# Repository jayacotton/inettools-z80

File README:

Here are the first hacks at getting some inet like tools running on
CP/M.

I am using (borrowing/stealing) code from several places.  See source for details.

A lot of hacking went into getting the code to run.  Probably some self inflicted
injuries along the way.

The programs of interest are linked by the Make file.

I am using z88dk and the tool chain.

You will need to hunt down and change the mac address in every file
you can find and in some cases a hard coded ip address.
I will get around to fixing this at a latter date.  

make clean; make ; make install  Gets the programs to build
and copies them to /var/www/html/

With this and apache2 you can get wget running from your 
CP/M machine.  

Programs in this build,  Note:  these don't work like there unix 
big brothers.  

	DIG.COM
		C>dig www.google.com                                                            
		WWW.GOOGLE.COM :172.217.6.36     
	IFCONFIG.COM
		C>ifconfig                                                                      
		inet 192.168.1.129 netmask 255.255.255.0                                        
		ether 98.76.b6.11.00.c4      
	MYGET.COM
		c>myget <filename>
		this will copy a file from your local http server at a
		hard coded address.  (you will need to change the address
		for your network).
	PING.COM
		C>ping www.nasa.gov                                                             
		------------PING_TEST_START-----------------------                              
		Send Ping Request to Destination (13.35.125.62 ) ID:1234  SeqNum:4321 CheckSum:a
		Reply from 13.35.125.62  ID:1234 SeqNum:4321  :data size 52 bytes               
                                                                                
		Send Ping Request to Destination (13.35.125.62 ) ID:1235  SeqNum:4322 CheckSum:8
		Reply from 13.35.125.62  ID:1235 SeqNum:4322  :data size 52 bytes               
                                                                                
		Send Ping Request to Destination (13.35.125.62 ) ID:1236  SeqNum:4323 CheckSum:6
		Reply from 13.35.125.62  ID:1236 SeqNum:4323  :data size 52 bytes               
                                                                                
		-----------PING TEST OK----------                                               
	TELNET.COM
		c>telnet <server name/inet address>
			bla bla bla
		exit (assumes your server does shell exit)
	WGET.COM
		c> wget http://<url or inet address> filename
		copies a file from the server to your CP/M box.

All of these programs are a bit shaky or just plain buggy.  

The socket libraries are kinda broken.  If you are used to BSD sockets you will get into 
trouble real fast.  I am thinking about fixing some of the more obvious bugs and mistakes
...maybe next month...  The main reason to fix these libs, is it then gets easier to port
code to CP/M.

WRT the h/w.

I coded all this to run with my bit banger SPI bus card and an Adafruit wiznet w5500 
ethernet board.  I am planning to build up a h/w SPI board soon, and will make a unified
driver for both cards.  If I can figure out how to do it (correctly) I will be able to
run the programs on ether SPI card with no modification (recompile) needed.  That would
be very nice to do.

Work to be done:

Fix the socket library.
Get some kind of timer code running with the ctc board.
Figure out a good select method.
Unified SPI driver.
Try to get the w5500 driver to work with the w5100 chip.  (it should but wont).

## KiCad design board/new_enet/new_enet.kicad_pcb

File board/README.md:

In this section we have the BOM for the MT011 board as built
for my needs.

For the best and current information about the MT011 board see
https://github.com/markt4311/MT011.git

Find here the mt011-bom.ods a spread sheet for the BOM of the board.
And the schematic (copied from above) MT011_SPI_WIZNET.pdf

I will include a picture of the board as built.

This board is now working on 18mhz cpu rc2014 systems.

```
--------------NOTICE---------------------
--------------NOTICE---------------------
--------------NOTICE---------------------
--------------NOTICE---------------------
--------------NOTICE---------------------
There is a small rework to get an access status led for the enet board.
Look at the schmatic, The resistor R2 leg that connects to pin 7
of U3 should be moved to pin 10 of U3.
--------------NOTICE---------------------
--------------NOTICE---------------------
--------------NOTICE---------------------
--------------NOTICE---------------------
--------------NOTICE---------------------
```

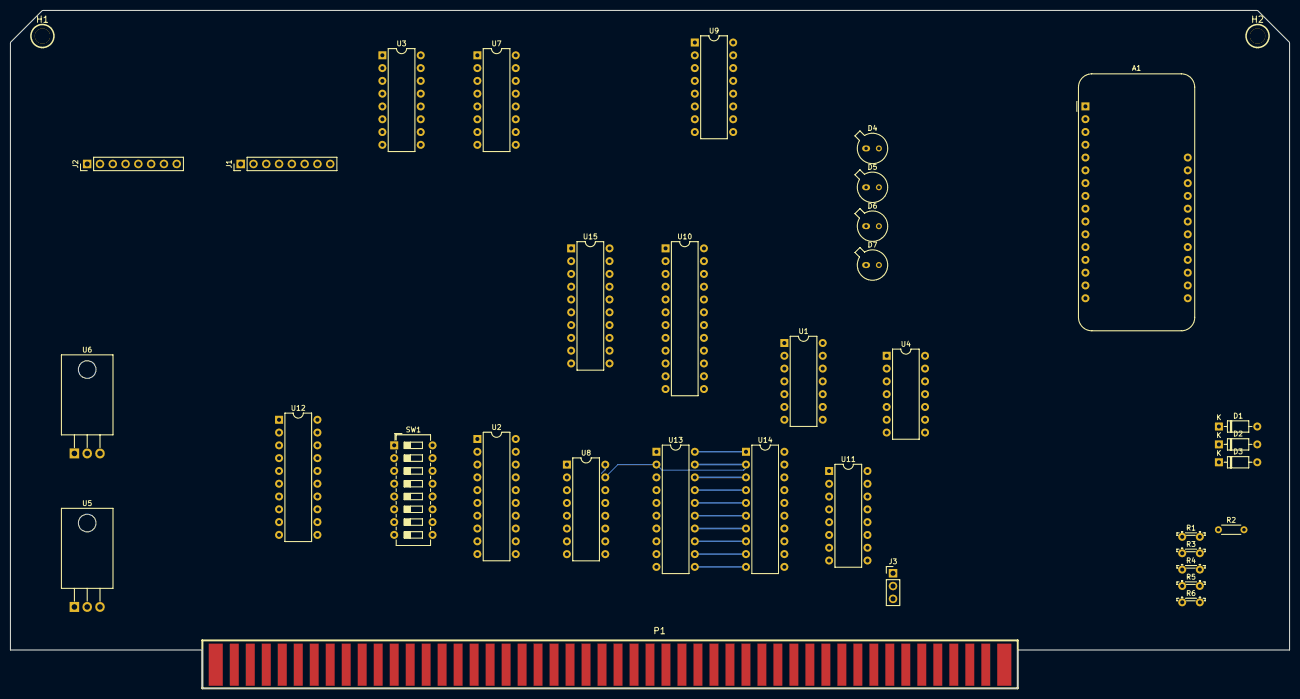
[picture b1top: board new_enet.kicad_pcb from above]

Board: 2 copper layers, 254.0 x 134.6 mm, 36 parts (0 on the bottom side), 64 nets.

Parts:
A1: Adafruit FeatherWing Ethernet board PN 3201; Adafruit_Feather
D1, D2, D3: 1N4148; D_DO-35_SOD27_P7.62mm_Horizontal
D4, D5, D6: yellow; TO-18-2_Window
D7: red; TO-18-2_Window
H1, H2: Ejector; s100-ejector
J1: FRAM socket; PinHeader_1x08_P2.54mm_Vertical
J2: SD Socket; PinHeader_1x08_P2.54mm_Vertical
J3: ClockSelect; PinHeader_1x03_P2.54mm_Vertical
P1: S100_MALE
R1: 20K; R_LDR_5.2x5.2mm_P3.5mm_Horizontal
R2: 4.7K; R_Axial_DIN0204_L3.6mm_D1.6mm_P5.08mm_Horizontal
R3, R4, R5, R6: 470; R_LDR_5.2x5.2mm_P3.5mm_Horizontal
SW1: SW_DIP_x08; SW_DIP_SPSTx08_Slide_6.7x21.88mm_W7.62mm_P2.54mm_LowProfile
U1: 74LS10; DIP-14_W7.62mm
U2: 74LS688; DIP-20_W7.62mm
U3: 74LS163; DIP-16_W7.62mm
U4: 74HC02; DIP-14_W7.62mm
U5: L7805; TO-220-3_Horizontal_TabDown
U6: SPX2920U-3.3_TO220; TO-220-3_Horizontal_TabDown
U7: 74LS138; DIP-16_W7.62mm
U8: 74LS595; DIP-16_W7.62mm
U9: 74LS175; DIP-16_W7.62mm
U10: 22V10; DIP-24_W7.62mm
U11: 74LS165; DIP-16_W7.62mm
U12, U13, U14, U15: 74LS245; DIP-20_W7.62mm

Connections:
+3V3: A1.2 (3V3), J1.8, J2.2, R1.1, U6.3 (VO)
+5V: R2.1, U1.14 (VCC), U2.20 (VCC), U3.16 (VCC), U4.14 (VCC), U5.3 (OUT), U6.1 (VI), U7.16 (VCC), U8.16 (VCC), U9.16 (VCC), U11.16 (VCC), U12.20 (VCC), U13.20 (VCC), U14.1 (A->B), U14.20 (VCC), U15.20 (VCC)
/0V: P1.50, P1.100
/+8V: P1.1, P1.51
BA0: U7.1 (A0), U12.2 (A0)
BA1: U7.3 (A2), U12.3 (A1)
BA2: U2.13 (P5), U12.4 (A2)
BA3: U2.6 (P2), U12.5 (A3)
BA4: U2.15 (P6), U12.6 (A4)
BA5: U2.4 (P1), U12.7 (A5)
BA6: U2.17 (P7), U12.8 (A6)
BA7: U2.2 (P0), U12.9 (A7)
BD0: U8.15 (QA), U9.13 (D3), U11.11 (D0), U13.2 (A0), U14.2 (A0)
BD1: U8.1 (QB), U11.12 (D1), U13.3 (A1), U14.3 (A1)
BD2: U8.2 (QC), U11.13 (D2), U13.4 (A2), U14.4 (A2)
BD3: U8.3 (QD), U9.12 (D2), U11.14 (D3), U13.5 (A3), U14.5 (A3)
BD4: U8.4 (QE), U9.4 (D0), U11.3 (D4), U13.6 (A4), U14.6 (A4)
BD5: U8.5 (QF), U9.5 (D1), U11.4 (D5), U13.7 (A5), U14.7 (A5)
BD6: U8.6 (QG), U11.5 (D6), U13.8 (A6), U14.8 (A6)
BD7: U8.7 (QH), U11.6 (D7), U13.9 (A7), U14.9 (A7)
GND: A1.4 (GND), D4.1 (K), D5.1 (K), D6.1 (K), D7.1 (K), J1.7, J2.3, SW1.1, SW1.2, SW1.3, SW1.4, SW1.5, SW1.6, SW1.7, SW1.8, U1.7 (GND), U2.1 (G), U2.8 (P3), U2.9 (R3), U2.10 (GND), U2.11 (P4), U2.12 (R4), U3.8 (GND), U4.3, U4.7 (GND), U4.8, U4.12, U5.2 (GND), U6.2 (GND), U7.8 (GND), U8.8 (GND), U9.8 (GND), U10.12 (GND), U11.8 (GND), U12.1 (A->B), U12.10 (GND), U12.19 (CE), U13.1 (A->B), U13.10 (GND), U14.10 (GND), U15.1 (A->B), U15.10 (GND), U15.19 (CE)
HIGH: R2.2, U3.10 (CET), U8.10 (~SRCLR), U11.10 (DS)
MISO: A1.13 (MISO), J1.4, J2.5, R1.2, U8.14 (SER)
MOSI: A1.12 (MOSI), J1.3, J2.6, U4.13
unnamed: D1.1 (K), U9.3 (~Q0)
unnamed: D2.1 (K), U9.6 (~Q1)
unnamed: D3.1 (K), U9.11 (~Q2)
unnamed: D4.2 (A), R3.2
unnamed: D5.2 (A), R4.2
unnamed: D6.2 (A), R5.2
unnamed: D7.2 (A), R6.2
unnamed: J3.2, U15.18 (B0)
unnamed: U1.12, U4.9
unnamed: SW1.16, U2.3 (R0)
unnamed: SW1.14, U2.5 (R1)
unnamed: SW1.12, U2.7 (R2)
unnamed: SW1.11, U2.14 (R5)
unnamed: SW1.13, U2.16 (R6)
unnamed: SW1.15, U2.18 (R7)
unnamed: U3.7 (CEP), U3.9 (~PE), U4.1
unnamed: U1.8, U3.3 (D0), U3.4 (D1)
unnamed: U1.4, U3.15 (TC)
unnamed: U1.6, U1.11, U3.1 (~MR)
unnamed: U7.11 (O4), U9.9 (Cp)
unnamed: U4.10, U8.13 (~OE)
unnamed: R3.1, U9.2 (Q0)
unnamed: R4.1, U9.7 (Q1)
unnamed: R5.1, U9.10 (Q2)
unnamed: R6.1, U9.15 (Q3)
unnamed: U3.5 (D2), U3.6 (D3), U3.11 (Q3), U4.2, U4.6, U11.15 (~CE)
unnamed: U4.11, U11.7 (~Q7)
SCK: A1.11 (SCK), J1.5, J2.4, U4.4, U8.11 (SRCLK)
SCLK: U3.2 (CP), U4.5, U8.12 (RCLK), U11.2 (CP), U15.2 (A0)
SEL: U2.19 (P=R), U7.5 (E2), U10.4 (I4)
/CS0: A1.10 (A5), D3.2 (A)
/CS2: D2.2 (A), J1.2
/IN_ENABLE: U10.19 (O5), U13.19 (CE)
/IORQ: U7.4 (E1), U10.16 (O8)
/OUT_ENABLE: U10.21 (O3), U14.19 (CE)
/RESET: A1.1 (~RESET), U9.1 (~Mr)
/SPI_RDNTR: U1.1, U7.13 (O2)
/SPI_RDTR: U1.2, U1.5, U1.9, U1.13, U7.12 (O3)
/SPI_WRTR: U1.3, U1.10, U7.15 (O0), U11.1 (~PL)
/WR: U7.2 (A1), U10.15 (O9)

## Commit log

2019-05-26 Add files via upload
    initial upload
2019-05-26 Update README.md
    Added more info.
2019-05-26 Update to exclude timer code. its busted now.
2019-05-26 Fixed htget to ignore timer code.
2019-05-26 Finel fixes, it runs now.
2019-05-26 removed README.CTC
2019-05-30 Changed device name to match hardware
2019-06-09 Tracking down printf problem
2019-09-19 Update README.md
    fix typo
2019-10-15 Updates to code base for new SPI select logic and support for SD card.
2019-10-29 Modified time code and update ntp/date to use RomWBW RTC interface.
2019-10-30 Clean out CTC driver code.
2019-10-30 Clean out old time, ctc, rtci2c code. Fix Makefile.
2019-10-30 Added round trip to ping.
2019-10-30 clearing out the weeds
2019-10-30 cleanup
2019-10-30 add pre built code.
2019-10-31 fix for lack of timer support
2019-10-31 update ping code to work on systems without timer support
2019-10-31 update for recent changes
2019-11-13 add code for daylight time.
2020-03-17 Removeing dead code from this push to reduce the size of exicutables
2020-03-17 update headers for code size reduction
2020-03-17 updated smaller binaries
2020-03-17 Updates to binary size
2020-03-17 Update README.md
    updated comments
2020-03-17 dead fileswq
2020-03-17 ops dont remove that one
2020-04-04 updated so make just builds what you want.
2020-04-05 tool for collecting mac address
2020-04-05 add built program
2020-04-05 mass update and added telnetd
2020-04-06 More fixes of makefile
2020-04-06 fix typo
2020-05-01 added rtc check
2020-05-01 fixes to rtc check
2020-05-01 more fixes for nist address
2020-05-03 Working on clock code
2020-05-03 for when you really need to know how long its been since last reboot.
2020-05-03 mass work on time code.
2020-05-03 and make file
2020-05-03 Add demo program
2020-05-03 still adding demo
2020-05-03 More work on time
2020-05-03 Add a way to set timezone
2020-05-03 mass updates to sysface and ntp.
2020-05-03 and makefile
2020-05-05 General bug fixing. Think I have date and today agreeing and ntp is setting the time correctly. Timezone now seems to display the correct value.
2020-05-05 and some exicutables
2020-05-06 updates so that code can work somewhere other than west coast of north america
2020-05-06 update commands a bit
2020-05-07 Overhaul timezone code to work with time zone codes
2020-05-08 workspace storage bug. don't crowd the nvram space.....
2020-05-08 fix bug in work space storage
2020-05-15 fix bug in selecting the nist server
2020-05-17 new program
2020-05-17 another new program
2020-05-17 Added CP/NET pseudo drive install support
2020-05-17 and some runable code
2020-05-17 added new commands
2020-05-18 Add link to CPNET repo
2020-05-18 added pragma to move stack to c000
2020-05-18 fixing stack problem
2020-05-19 Better code, less busy screen
2020-05-24 Fix stack address, clean up compile warnings
2020-05-24 Stack pointer fixup
2020-06-03 forgot this one
2020-06-03 fix the year bug
2020-06-03 fix compile warning
2020-06-03 this should not be here
2020-06-03 add pre built programs
2021-03-19 document the board
2021-03-19 added more parts to the list
2021-03-22 fix a typo
2021-03-26 Adding FRAM support and fixing bugs
2021-03-26 update exicutables
2021-03-26 add FRAM support in lew of NVRAM
2021-03-26 add notes about FRAM
2021-03-29 adding new functions
2021-03-29 fix ether address bug
2021-04-01 add bsd like host file
2021-04-01 adding bsd host file
2021-04-02 remove extra build
2021-04-03 working on BSD style hosts
2021-04-03 add sample file
2021-04-03 Add updated binaries
2021-04-03 Update README.md
    clean up readme
2021-04-03 Update README.md
    more cleaning
2021-04-09 reorganize fram function into general inet config code
2021-04-09 fix compile bugs and test DISK build
2021-04-10 integrate and combine FRAM NVRAM and DISK into libinet
2021-04-10 replaced with libinet
2021-04-10 more bug fixing, clean up compile warnings
2021-04-10 include CPNET struct
2021-04-13 modifiy to use bsd style hosts file
2021-04-14 debug work on z88dk bug 1759
2021-04-14 new function
2021-04-15 add html parser
2021-04-17 debug myget and htlist
2021-04-22 Debug startup, buffer overrun, compile warnings general code work
2021-04-24 Debug a console I/O problem
2021-08-22 lower case switch
2022-02-01 updates for multi platform build
2022-02-01 add build configuration
2022-02-01 Make multi platform
2022-02-04 Add files via upload
    adding s100 board
2022-02-04 update schmatic
2022-02-19 finish 22v10
2022-10-27 minor fix to state machine
2022-11-06 Adding TOD support for s100 bus
2022-11-06 Bug fix for ntp TOD randomness
2022-11-07 Fixing timer issues
2022-11-08 spi burst read
2022-11-16 fixed build flags for linux
2022-11-16 update net addr buffer
2023-03-20 new layout
2025-10-11 Clean up repository: remove build artifacts, add .gitignore, and include development improvements…
2025-10-11 Remove personal information and cache files
    - Remove KiCad fp-info-cache files (can be regenerated)
    - Clean personal paths from board/new_enet/new_enet.net
    - Personal information and specific user paths have been sanitized
2025-10-11 Add 2025 enhancements documentation
    Document the significant improvements made to INET tools for
    RC2014/RomWBW/MT011/W5500/FRAM systems including:
    - Tool version improvements (IFCONFIG v1.9, MAC v1.1)
    - System integration enhancements
    - Repository quality improvements
    - Build system cleanup
2025-10-12 Update to add manual ip entry
